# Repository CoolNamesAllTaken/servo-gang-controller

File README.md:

# servo-gang-controller
Arduino-based controller used to control eight PWM servos from a single PWM input channel

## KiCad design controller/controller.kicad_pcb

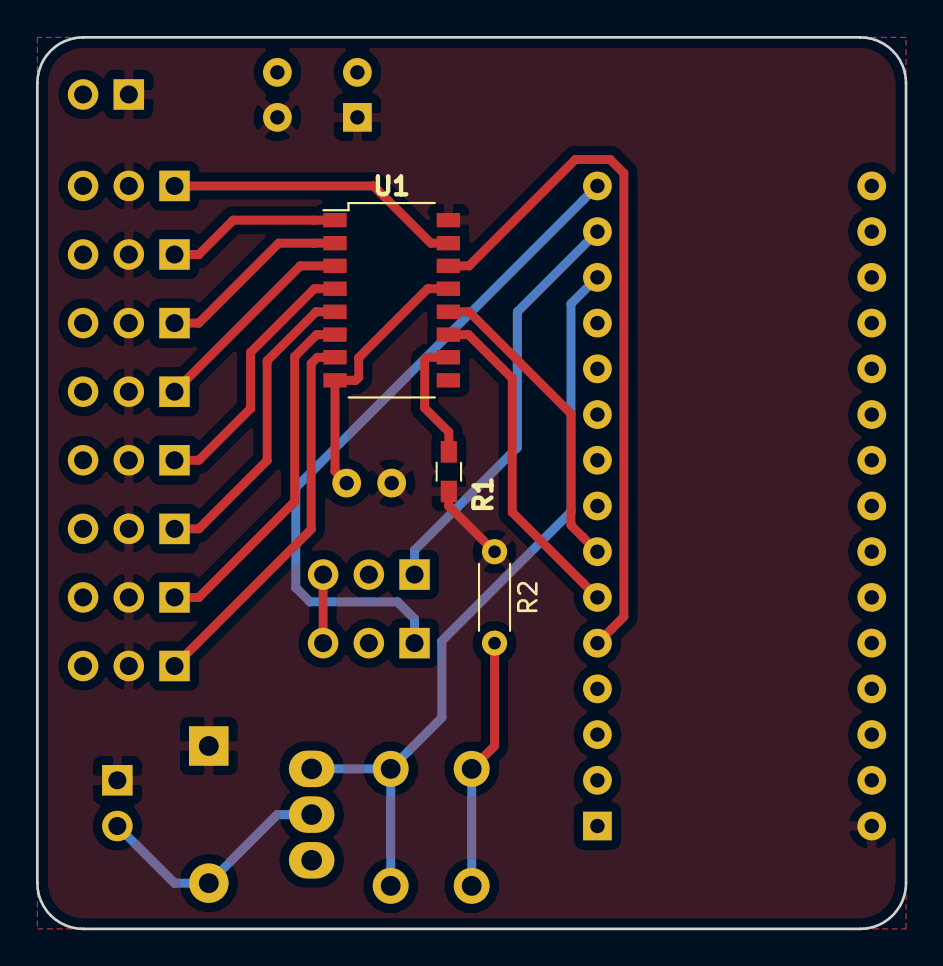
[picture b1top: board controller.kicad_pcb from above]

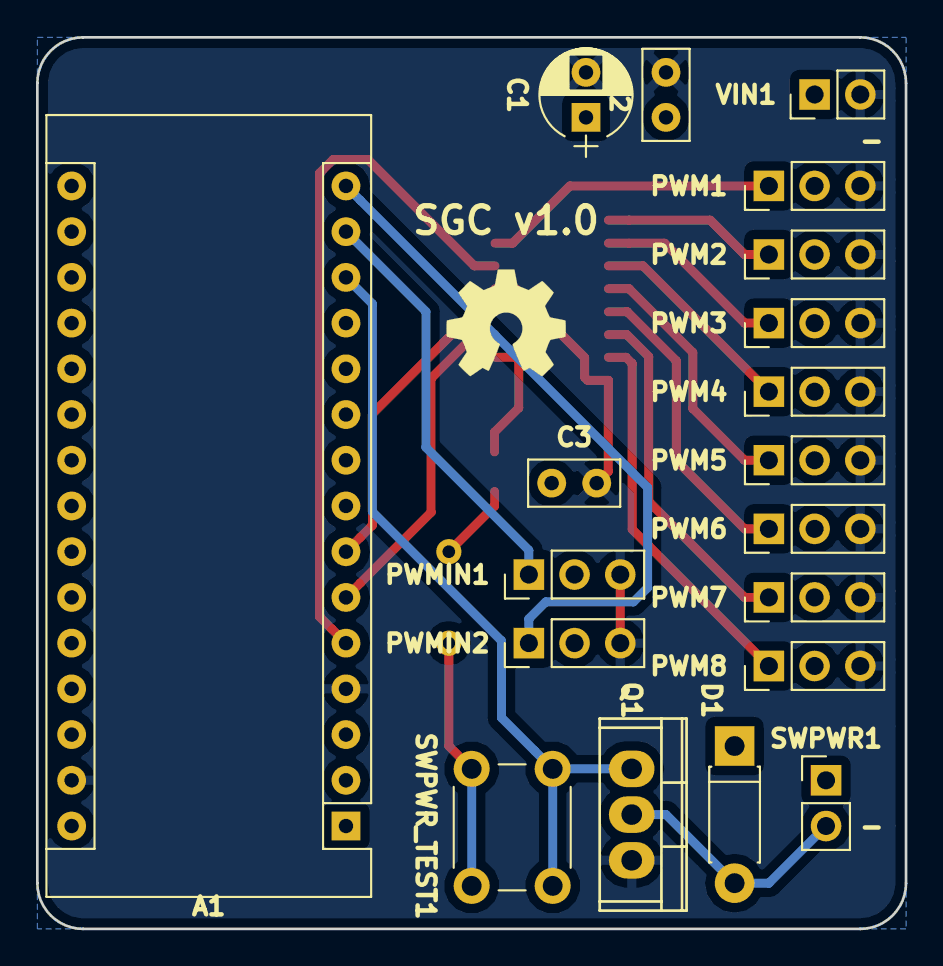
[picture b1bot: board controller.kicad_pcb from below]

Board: 2 copper layers, 48.3 x 49.5 mm, 22 parts (19 on the bottom side), 19 nets.

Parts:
A1: Arduino_Nano_v3.x; Arduino_Nano
C1: 100uF; CP_Radial_D5.0mm_P2.50mm
C2: 10uF; C_Disc_D5.0mm_W2.5mm_P2.50mm
C3: 0.1uF; C_Disc_D5.0mm_W2.5mm_P2.50mm
D1: D; D_DO-41_SOD81_P7.62mm_Horizontal
PWM1, PWM2, PWM3, PWM4, PWM5, PWM6, PWM7, PWM8: Conn_01x03_Male; Pin_Header_Straight_1x03_Pitch2.54mm
PWMIN1, PWMIN2: Conn_01x03_Male; Pin_Header_Straight_1x03_Pitch2.54mm
Q1: Q_NJFET_GDS; TO-220
R1: 10K; R_0603_HandSoldering
R2: 3K3; R_Axial_DIN0204_L3.6mm_D1.6mm_P5.08mm_Horizontal
SWPWR1: Conn_01x02_Male; Pin_Header_Straight_1x02_Pitch2.54mm
SWPWR_TEST1: SW_Push; SW_PUSH_6mm
U1: 74HC595; SOP-16_4.4x10.4mm_Pitch1.27mm
VIN1: Conn_01x02_Male; Pin_Header_Straight_1x02_Pitch2.54mm

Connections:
+5V: A1.30, C1.1, C2.1, C3.1, D1.1, PWM1.2, PWM2.2, PWM3.2, PWM4.2, PWM5.2, PWM6.2, PWM7.2, PWM8.2, R1.2, R2.1, SWPWR1.1, U1.16, VIN1.1
GND: A1.4, A1.29, C1.2, C2.2, C3.2, PWM1.3, PWM2.3, PWM3.3, PWM4.3, PWM5.3, PWM6.3, PWM7.3, PWM8.3, PWMIN1.3, PWMIN2.3, Q1.3, U1.8, U1.13, VIN1.2
unnamed: A1.5, U1.14
unnamed: A1.6, U1.11
unnamed: A1.7, U1.12
unnamed: A1.13, Q1.1, SWPWR_TEST1.1
unnamed: A1.14, PWMIN1.1
unnamed: A1.15, PWMIN2.1
unnamed: D1.2, Q1.2, SWPWR1.2
unnamed: PWM1.1, U1.15
unnamed: PWM2.1, U1.1
unnamed: PWM3.1, U1.2
unnamed: PWM4.1, U1.3
unnamed: PWM5.1, U1.4
unnamed: PWM6.1, U1.5
unnamed: PWM7.1, U1.6
unnamed: PWM8.1, U1.7
unnamed: R1.1, U1.10
unnamed: R2.2, SWPWR_TEST1.2

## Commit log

2019-01-12 Make shift register output basic slow square wave
2019-01-12 Make servos go back and forth
2019-02-12 Add hardware files
2019-02-14 Implements bomb drop functionality, but interrupts cause twitching
2019-04-03 Clean up gang controller code
2019-04-07 Make competition ready
    * resolve twitching issue by restructuring ISR
2020-08-02 Dump leftovers
